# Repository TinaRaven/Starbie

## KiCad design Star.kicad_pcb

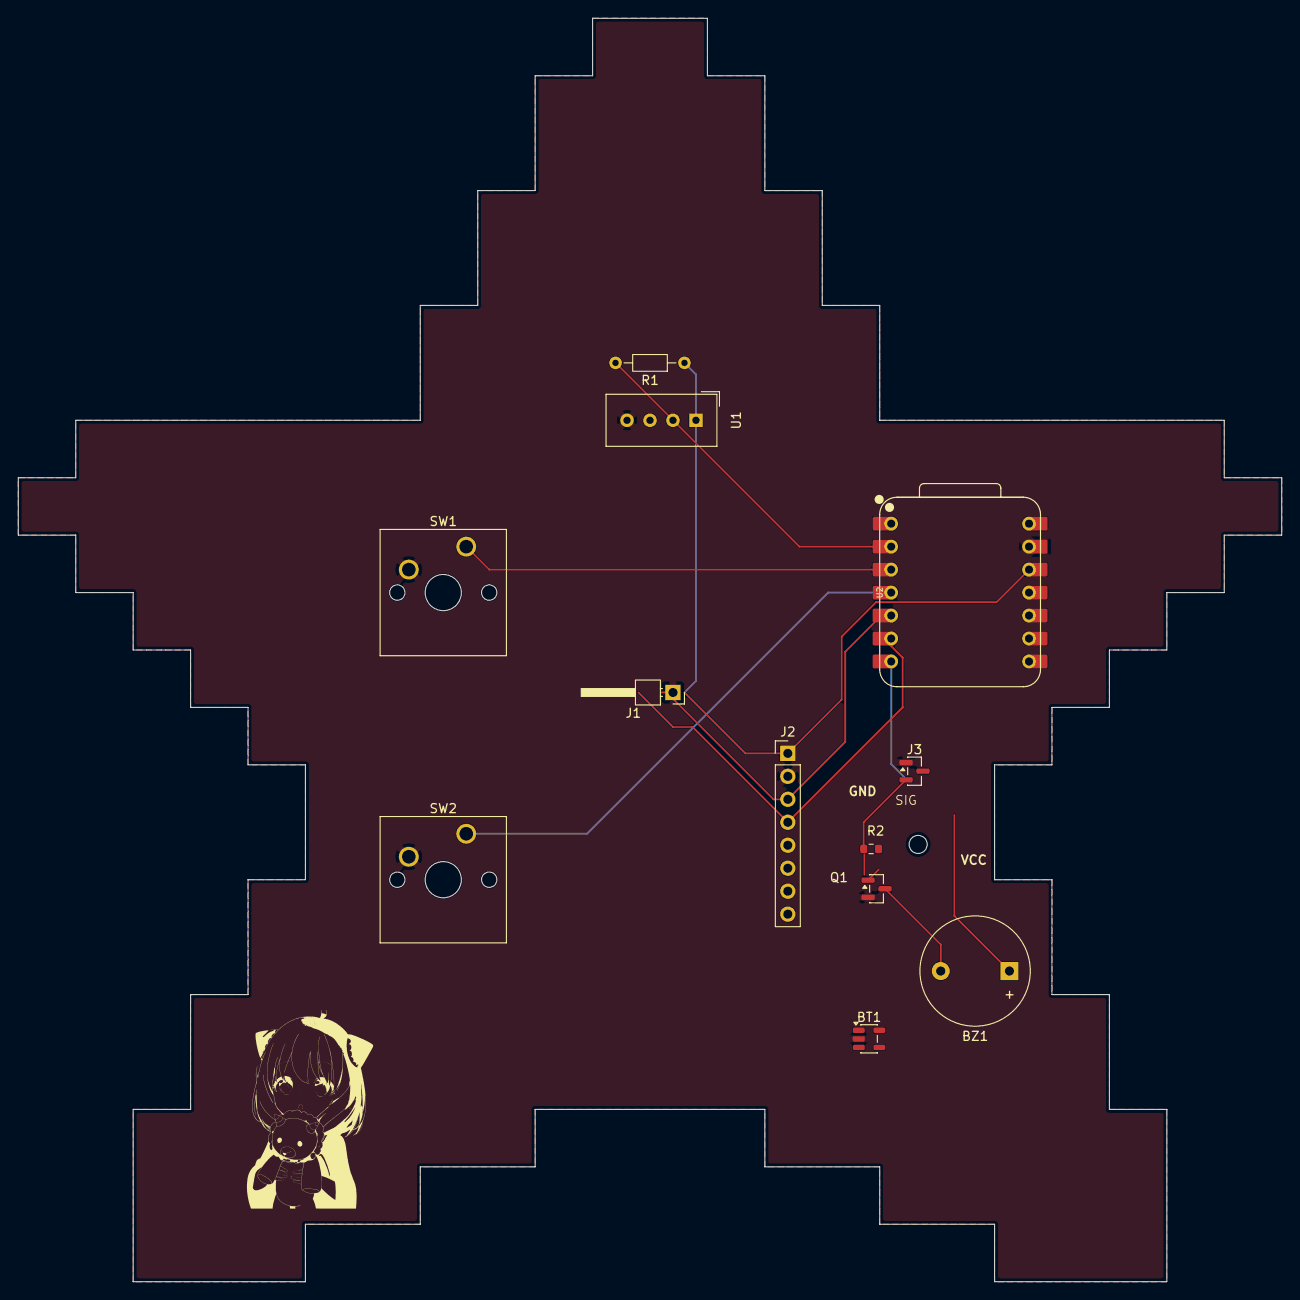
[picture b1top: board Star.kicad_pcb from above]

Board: 2 copper layers, 139.7 x 139.7 mm, 12 parts (0 on the bottom side), 10 nets.

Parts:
BT1: Battery; SOT-23-5
BZ1: Buzzer; Buzzer_12x9.5RM7.6
J1: Conn_01x04_Pin; PinHeader_1x01_P2.54mm_Horizontal
J2: Conn_01x08_Pin; PinHeader_1x08_P2.54mm_Vertical
J3: Conn_01x03_Pin; SOT-23
Q1: MMBT2222A; SOT-23
R1: 10k; R_Axial_DIN0204_L3.6mm_D1.6mm_P7.62mm_Horizontal
R2: 1k; R_0603_1608Metric
SW1, SW2: SW_Push; SW_Cherry_MX_1.00u_PCB
U1: DHT11; Aosong_DHT11_5.5x12.0_P2.54mm
U2: XIAO-ESP32-C3-SMD; XIAO-ESP32-C6-DIP

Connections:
+3.3V: BZ1.1 (+), J2.1, J3.3, R1.1, U1.1 (VDD), U2.12 (3V3_OUT)
/DHT11 DATA: R1.2, U1.2 (DATA), U2.2 (D1)
/GPIO2: SW1.1, U2.3 (D2)
/GPIO3: SW2.1, U2.4 (D3)
/SCL: J2.3, U2.5 (D4)
/SDA: J2.4, U2.6 (D5)
/SIG: J3.2, R2.1, U2.7 (D6)
GND: BT1.2 (-), J1.1 (Pin_1_1), J2.2, J3.1, Q1.2 (E), SW1.2, SW2.2, U1.4 (GND), U2.13 (GND)
unnamed: BZ1.2 (-), Q1.3 (C)
unnamed: Q1.1 (B), R2.2
